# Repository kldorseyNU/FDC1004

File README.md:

# FDC1004 Capacitance Reading and Breakout Board Hardware 

This library provides basic functionality for the FDC1004 Capacitance to Digital Sensor. According to the datasheet, the FDC1004 provides femto-farad precision for measuring capacitances up to 115 pF in increments of 500 aF. The .ino files in examples demonstrate reading continuous values, triggered single values for multiple channels, and differential measurements. 

The breakout board provides shielded capacitance readings on four channels. Off board, each channel is shielded with a micro-coax connector (U.FL), and the shealth can be connected to either GND (for passive shielding) or SHLD (for active shielding) using a 0 $\Omega$ resistor soldered to the board. The board schematic and PCB files are included in the BreakoutBoard directory in this repository. Please see the Hardware file for more information about the breakout board design.

## Hardware

 * A 3.3 V microcontroller board. The FDC1004 is incompatible with 5 V microcontrollers without additional care for the I2C bus voltage!
 * TI FDC1004: https://www.ti.com/product/FDC1004
 * 2 1.8k Ohm resistors to pull up SDA and SCL pins on I2C line (some microcontroller breakout boards may already have these on board)
 * A few non-polarized (e.g., ceramic) capacitors for test, in the range of 5 pF to 100 pF
 
## Limitations
 * This code has only been tested on the ESP32, ESP32-S2, and ESP32-S3 microcontroller breakout boards from Adafruit. It may not work on other 3.3 V microcontrollers such as the Adafruit Nano or Sparkfun Redboards that have 3.3 V logic levels. 
 * There is a potential bug when the FDC1004 is reading single (not repeated) measurements where it will read incorrectly. If you are getting unexpected behavior from the single read example, or no reading, push the continuous example first and then the single read example.

## Single-ended capacitance (channel to ground) or differential (channel to channel) readings: 
 * If first pin and second pin in configureMeasurement and triggerMeasurement functions are the same, it assumes a sigle-ended measurement
 * Otherwise, it assumes a differential measurement between those pins.
 * The convenience functions in the .cpp file (written by Beshaya) set the measurement type (single or continuous, which channels, measurement number/register)
 * Capacitors must always be placed from channel to ground. In differential measurements, they are still read by the difference between capacitance channels to ground. 

 ## Documentation on example functions
 
### float absoluteCapacitance(uint8_t measSlot, uint8_t chanA, uint8_t chanB, uint8_t measType, uint8_t * capdacPtr)
 * Calculates the absolute capaciance capacitanceAbsolute (relative + capdac) read off the FDC1004

 #### Parameters: 
 * measSlot : the measurement "slot" or number. This can be arbitrary between 0 and 3, or measA, measB... for convenience
 * chanA : the first pin you wish to measure capacitance to ground. Use pin definitions above for convenience.
 * chanB : the second pin you wish to measure capacitance to ground. Due to limitations of the FDC1004, chanB must be the same or greater value to chanA. Setting to the same value as chanA will set up a single-ended measurement. Setting at a higher value will set up a differential measurement. 
 * measType : Single (0) or repeated (1). Use measSingl and measCont for convenience. 
 * capdacPtr : A pointer to the global capdac value for that measurement. Labeled capdacA, capdacB... for convenience

 #### returns capacitanceAbsolute

* Notes: Calls configTrigRead in the case of a single measurement. Calls relativeCapacitance value in the case of a repeated measurement. If the returned capacitanceRelative reading is out of the +/- 15 pF limits for the FDC1004, it will call setCAPDAC. It converts capdac to a capacitance value in pF and adds to relative capacitance to find capacitanceAbsolute. If setCAPDAC was called, it will set the value of to capacitanceAbsolute -1

### float relativeCapacitance(uint8_t measSlot)
  * Reads the relative capacitance capacitanceRelative

#### Parameters: 
  * measSlot : the measurement "slot" or number. This can be arbitrary between 0 and 3, or measA, measB... for convenience

#### returns capacitanceRelative

* Notes: calls fdc.readMeasurement to read a 32-bit value (24-bit capacitance with 8 trailing zeroes, as per FDC1004 documentation) and convert into a capacitance reading with the ratio 15 pF/ 32676. The 16 most significant bits (MSB) are the only ones needed for the capacitance reading, since the measurement resolution is 0.5 fF and the max range is 30 pF. A 16 bit value in two's complement ranges from -32768 to 32767 (2^15 - 1) (i.e., resolution of ~0.46 fF with +/- 15 pF range). Therefore, we don't need to calculate the capacitance using the LSB since the most significant bit of LSB is below the measurement resolution/noise floor. We do still need to read LSB since the FDC1004 is expecting it to be read before the next measurement. The convenience functions in the .cpp file take care of this read.

### uint8_t setCAPDAC(uint8_t measSlot, uint8_t chanA, uint8_t chanB, uint8_t measType, uint8_t * capdacPtr)
* Resets capdac value. Will only execute if the measurement is single-ended (chanA and chanB are the same), because capdac cannot be set for a differential measurement.

#### Parameters:  
* measSlot : the measurement "slot" or number. This can be arbitrary between 0 and 3, or measA, measB... for convenience
* chanA : the first pin you wish to measure capacitance to ground. Use pin definitions above for convenience.
* chanB : the second pin you wish to measure capacitance to ground. Due to limitations of the FDC1004, chanB must be the same or greater value to chanA. Setting to the same value as chanA will set up a single-ended measurement. Setting at a higher value will set up a differential measurement. 
* measType : Single (0) or repeated (1). Use measSingl and measCont for convenience. 
* capdacPtr : the pointer to the global capdac associated with the measurement in measSlot

#### returns *capdacPtr (the dereference to the pointer to the global capdac associated with that measurement)

* Notes: Resets capdac to 0 and calls configTrigRead to read the relative value. While the new capdac value has not been found, it calls adjustCAPDAC, then calls configTrigRead in a loop until the timeout value (set to 30 by default). If a new capdac value is not found, it defaults to 0.

### uint8_t adjustCAPDAC(float capacitanceRelative, uint8_t * capdacPtr)
* Adjusts or increments capdac value and returns a flag stating whether it successfully reset.
 
#### Parameters: 
* capacitanceRelative : the relative capacitance reading fom the FDC
* capdacPtr : the pointer to the global capdac associated with the measurement in measSlot

#### returns capdacFlag, which says whether or not the capdac has been successfully reset.

* Notes: If the capdac is in range, it will try to find the capdac value that brings capacitanceRelative as close to 0 as possible to give the largest potential range, then return 0 to signal that capdac has been reset successfully. If capdac is not in range, it will incremenet or decrement capdac by 5 (15.625 pF) to bring it to the next range, then return 1 to signal that capdac needs to be set again.

### float configTrigRead(uint8_t measSlot, uint8_t chanA, uint8_t chanB, uint8_t measType, uint8_t capdac)
 * Configures and triggers the measurement and reads relative capacitance

 #### Parameters: 
 * measSlot : the measurement "slot" or number. This can be arbitrary between 0 and 3, or measA, measB... for convenience
 * chanA : the first pin you wish to measure capacitance to ground. Use pin definitions above for convenience.
 * chanB : the second pin you wish to measure capacitance to ground. Due to limitations of the FDC1004, chanB must be the same or greater value to chanA. Setting to the same value as chanA will set up a single-ended measurement. Setting at a higher value will set up a differential measurement. 
 * measType : Single (0) or repeated (1). Use measSingl and measCont for convenience. 
 * capdac : the global capdac value associated with that measurement.

 #### returns capacitanceRelative

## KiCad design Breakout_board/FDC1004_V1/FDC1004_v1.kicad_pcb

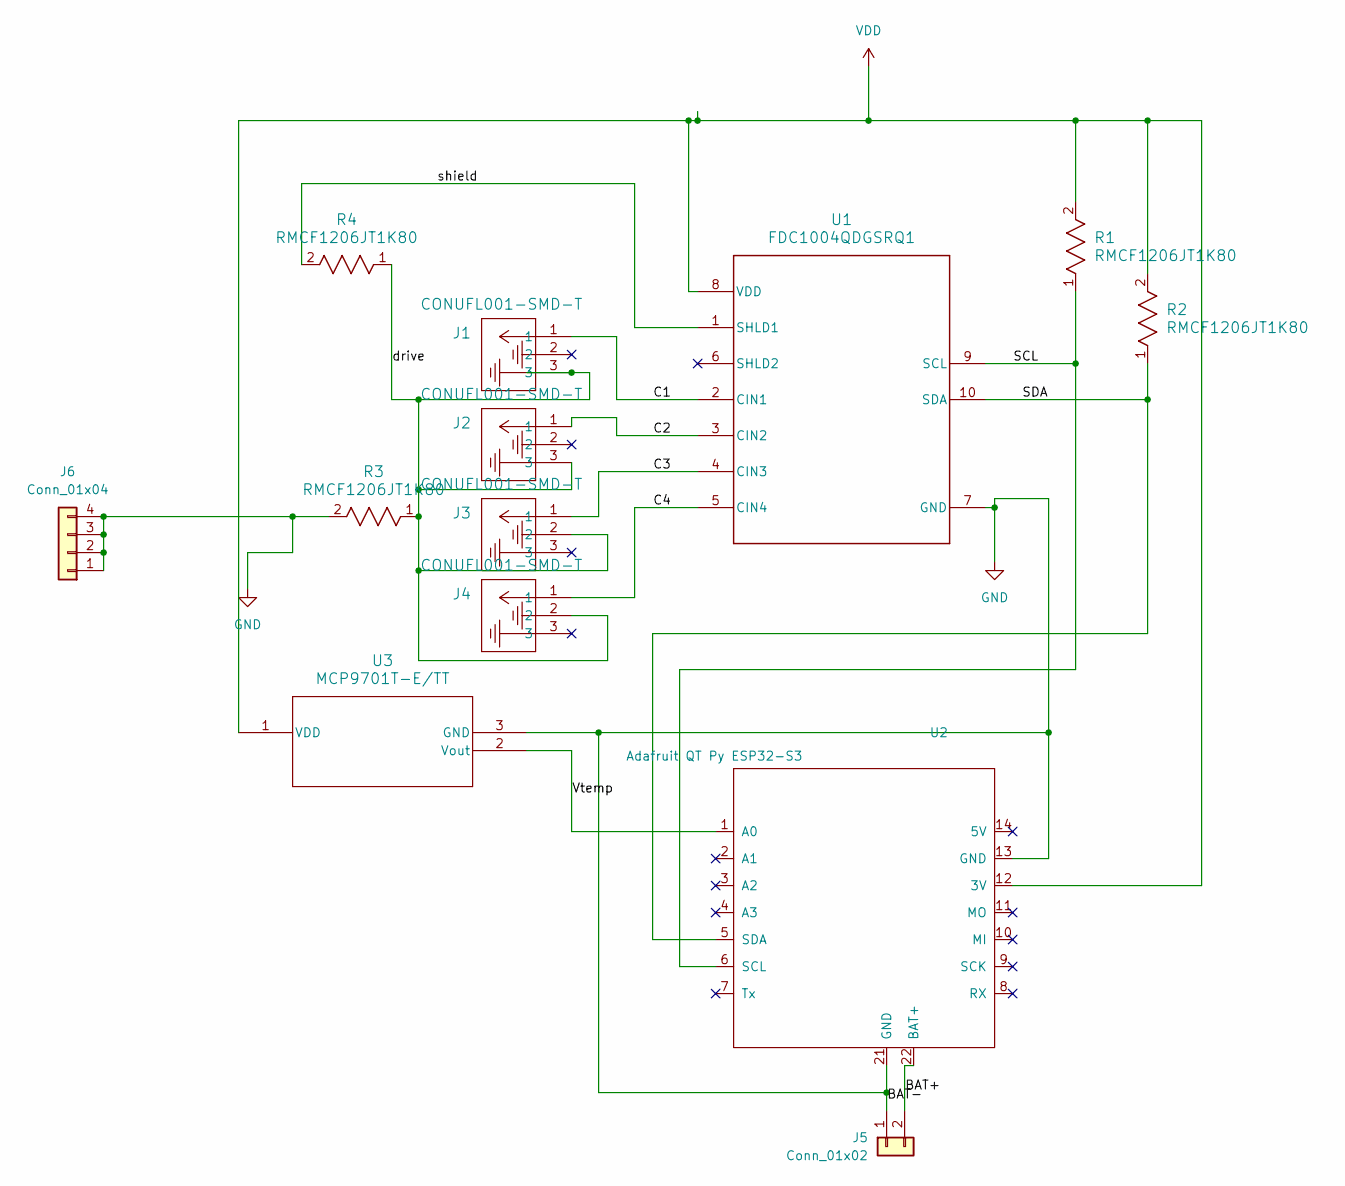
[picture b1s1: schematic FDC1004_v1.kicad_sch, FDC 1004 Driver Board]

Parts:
J1, J2, J3, J4: CONUFL001-SMD-T; CONN1_CONUFL_TEC
J5: Conn_01x02; PinHeader_1x02_P2.54mm_Vertical
J6: Conn_01x04; PinHeader_1x04_P2.54mm_Vertical
R1, R2, R3, R4: RMCF1206JT1K80; STA_RMCF1206_STC
U1: FDC1004QDGSRQ1; FDC1004DGS0010A_M
U2: Adafruit QT Py ESP32-S3; Ada_ESP32-S3_noPSRAM
U3: MCP9701T-E/TT; SOT-23_MC_MCH-M

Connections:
/BAT+: J5.2, U2.22 (BAT+)
/C1: J1.1, U1.2 (CIN1)
/C2: J2.1, U1.3 (CIN2)
/C3: J3.1, U1.4 (CIN3)
/C4: J4.1, U1.5 (CIN4)
/SCL: R1.1, U1.9 (SCL), U2.6 (SCL)
/SDA: R2.1, U1.10 (SDA), U2.5 (SDA)
/Vtemp: U2.1 (A0), U3.2 (Vout)
/drive: J1.3, J2.3, J3.2, J4.2, R3.1, R4.1
/shield: R4.2, U1.1 (SHLD1)
GND: J5.1, J6.1, J6.2, J6.3, J6.4, R3.2, U1.7 (GND), U2.13 (GND), U2.21 (GND), U3.3 (GND)
VDD: R1.2, R2.2, U1.8 (VDD), U2.12 (3V), U3.1 (VDD)

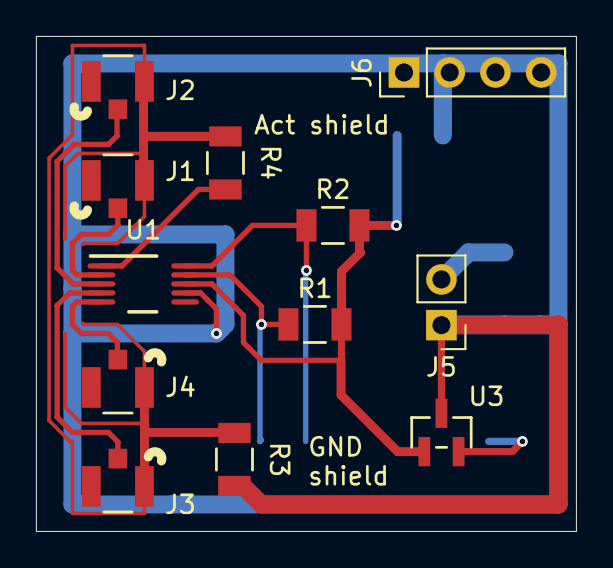
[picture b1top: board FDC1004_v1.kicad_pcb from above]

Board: 2 copper layers, 30.0 x 27.5 mm, 13 parts (1 on the bottom side), 12 nets.

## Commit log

2024-07-22 update READme and CAPDAC calculations
2024-07-22 remove out of date keywords file
2024-07-22 remove deprecated _raw ino file
2024-07-22 add to READme
2024-07-22 fix typos
2024-07-22 update read function
2024-07-23 fix CAPDAC bug
2024-07-23 add absoluteCapacitance function
2024-07-23 refactor functions
2024-07-23 add reset
2024-07-23 fix absoluteCapacitance
2024-07-23 fix readMeasurement to wait for FDC
2024-07-23 add adjustable rate
2024-07-23 fix cpp file
2024-07-23 add read rate
2024-07-24 add multichannel read example
2024-07-24 add multi-channel read example
2024-07-24 update setCAPDAC
2024-07-24 add repeated example
2024-07-24 add differential example
2024-07-24 update SETCAPDAC function
2024-07-24 remove outdated FDC1004 example
2024-07-24 update README formatting
2024-07-25 Update FDC1004.cpp
    remove extraneous comment
2024-07-25 Update FDC1004.cpp
    Remove extraneous Wire.write
2024-07-31 add I2C device check to setup
2024-08-24 Create Hardware.txt
    Description of the FDC1004 breakout board
2024-08-24 Rename Hardware.txt to Hardware.md
2024-08-24 add Kicad files for breakout board
2024-08-24 Update Hardware.md
    Add photo of v0 board
2024-08-28 update multi channel read for I2C address check
2024-08-29 update board files
2024-08-29 Update Hardware.md
    Update instructions to match the new board layout
2024-08-29 Update Hardware.md
    Fix spelling mistake
2024-09-22 add power on check sketch
2024-10-18 Add files for ROS node
